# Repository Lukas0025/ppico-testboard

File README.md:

# PPICO V1 Test Board
Simple test board for ppico satellite project. Can be used as sattelite testboard and groud station. The board contains two ports for i2c devices and one port for programming and debugging. The board contains one lorawan transceiver, attiny85 as MCU, coin cell battery for power supply and PCB antenna for easy use, or connector for external antenna.

The board was designed to be usable as a LoRaWAN node.

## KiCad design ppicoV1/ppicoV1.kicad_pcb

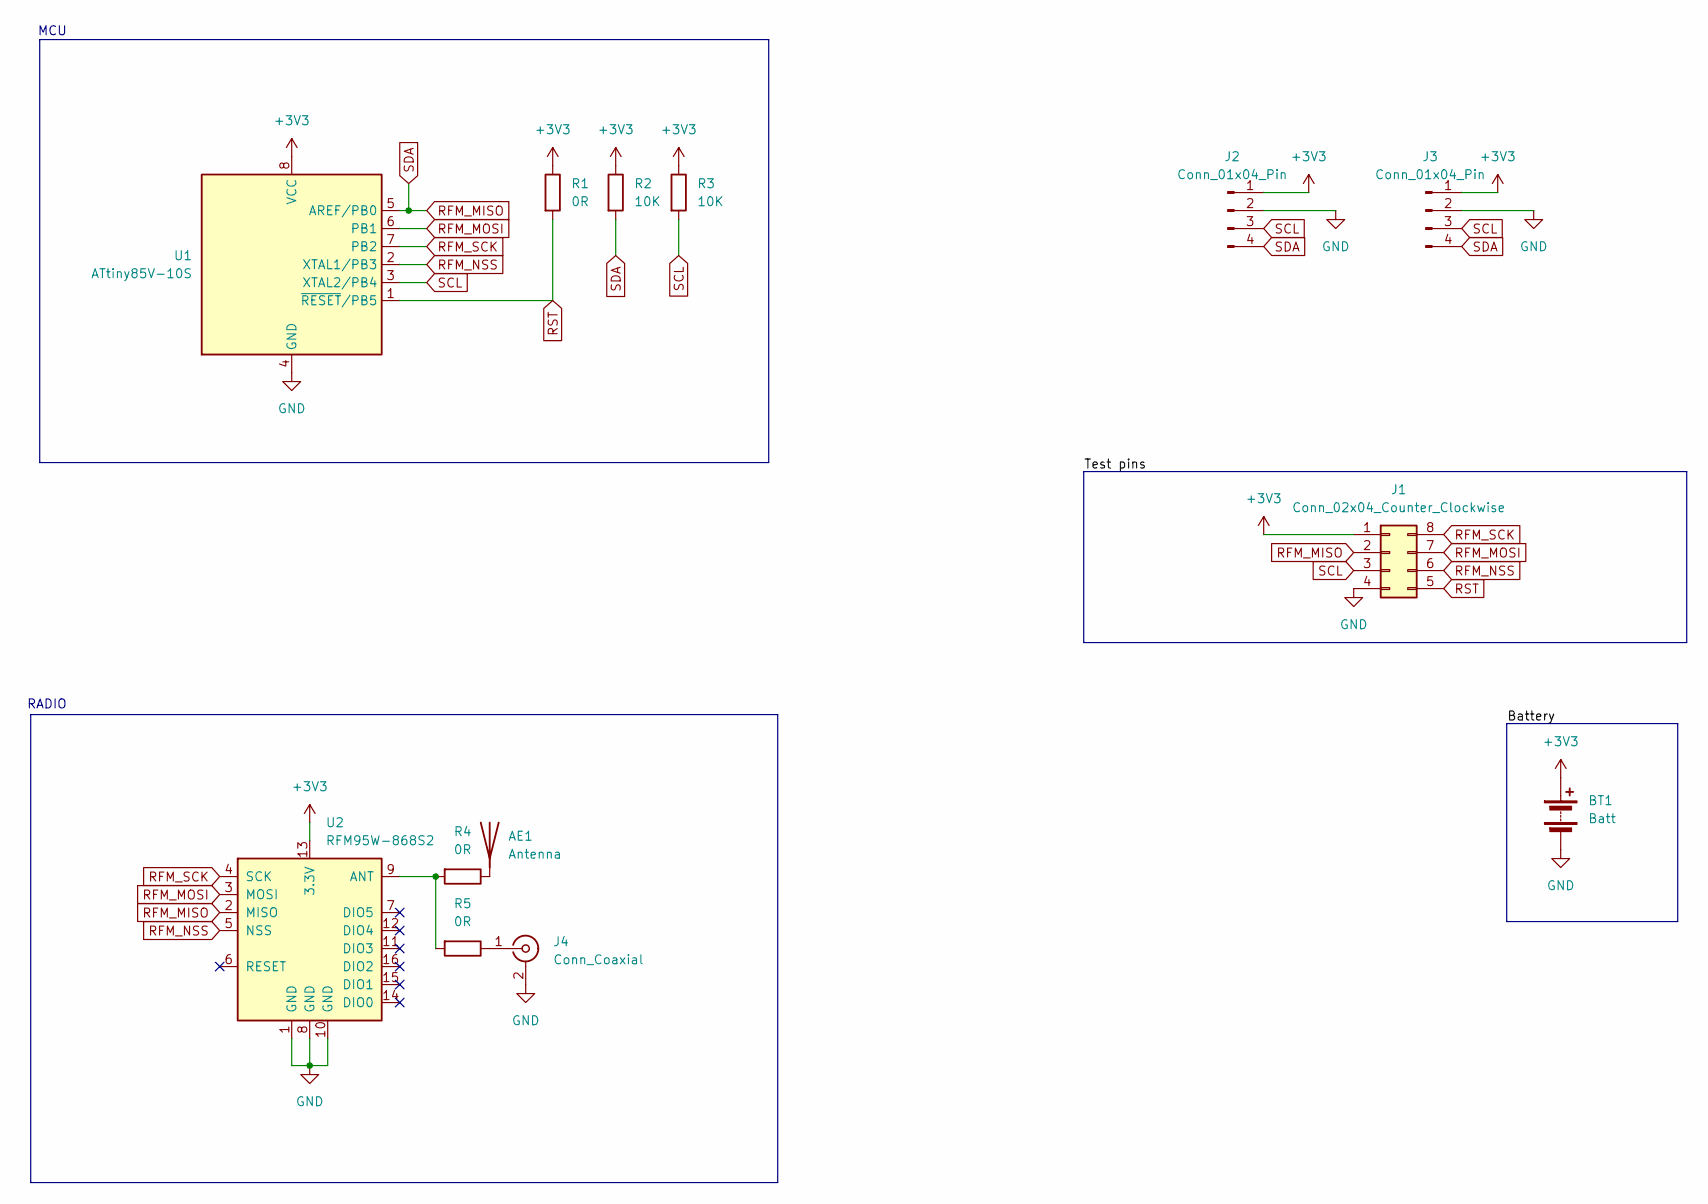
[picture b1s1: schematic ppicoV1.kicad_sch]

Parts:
AE1: Antenna; Texas_SWRA416_868MHz_915MHz
BT1: Batt; BatteryHolder_MYOUNG_BS-07-A1BJ001_CR2032
J1: Conn_02x04_Counter_Clockwise; PinHeader_2x04_P2.54mm_Vertical
J2, J3: Conn_01x04_Pin; PinHeader_1x04_P2.54mm_Vertical
J4: Conn_Coaxial; U.FL_Molex_MCRF_73412-0110_Vertical
R1, R4, R5: 0R; C_0805_2012Metric_Pad1.18x1.45mm_HandSolder
R2, R3: 10K; C_0805_2012Metric_Pad1.18x1.45mm_HandSolder
U1: ATtiny85V-10S; SOIC-8_5.3x5.3mm_P1.27mm
U2: RFM95W-868S2; HOPERF_RFM9XW_SMD

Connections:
+3V3: BT1.1 (+), J1.1, J2.1, J3.1, R1.1, R2.1, R3.1, U1.8 (VCC), U2.13 (3.3V)
GND: BT1.2 (-), J1.4, J2.2, J3.2, J4.2 (Ext), U1.4 (GND), U2.1 (GND), U2.8 (GND), U2.10 (GND)
unnamed: AE1.1 (A), R4.1
unnamed: J4.1 (In), R5.1
unnamed: R4.2, R5.2, U2.9 (ANT)
RFM_MISO: J1.2, J2.4, J3.4, R2.2, U1.5 (AREF/PB0), U2.2 (MISO)
RFM_MOSI: J1.7, U1.6 (PB1), U2.3 (MOSI)
RFM_NSS: J1.6, U1.2 (XTAL1/PB3), U2.5 (NSS)
RFM_SCK: J1.8, U1.7 (PB2), U2.4 (SCK)
RST: J1.5, R1.2, U1.1 (~RESET/PB5)
SCL: J1.3, J2.3, J3.3, R3.2, U1.3 (XTAL2/PB4)

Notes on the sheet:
MCU
RADIO

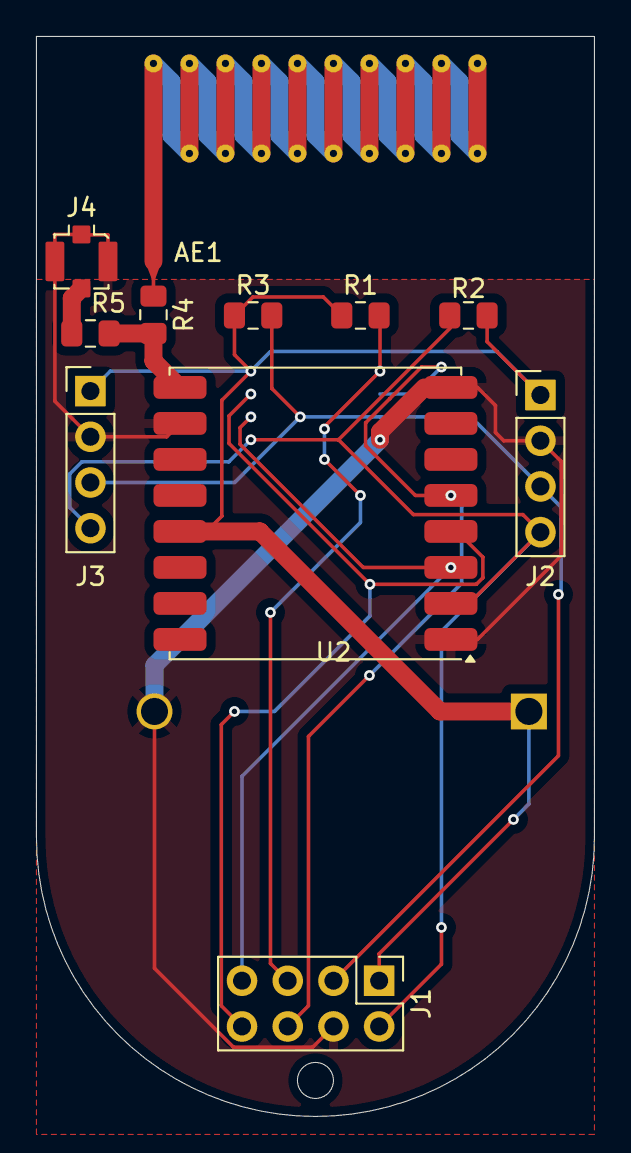
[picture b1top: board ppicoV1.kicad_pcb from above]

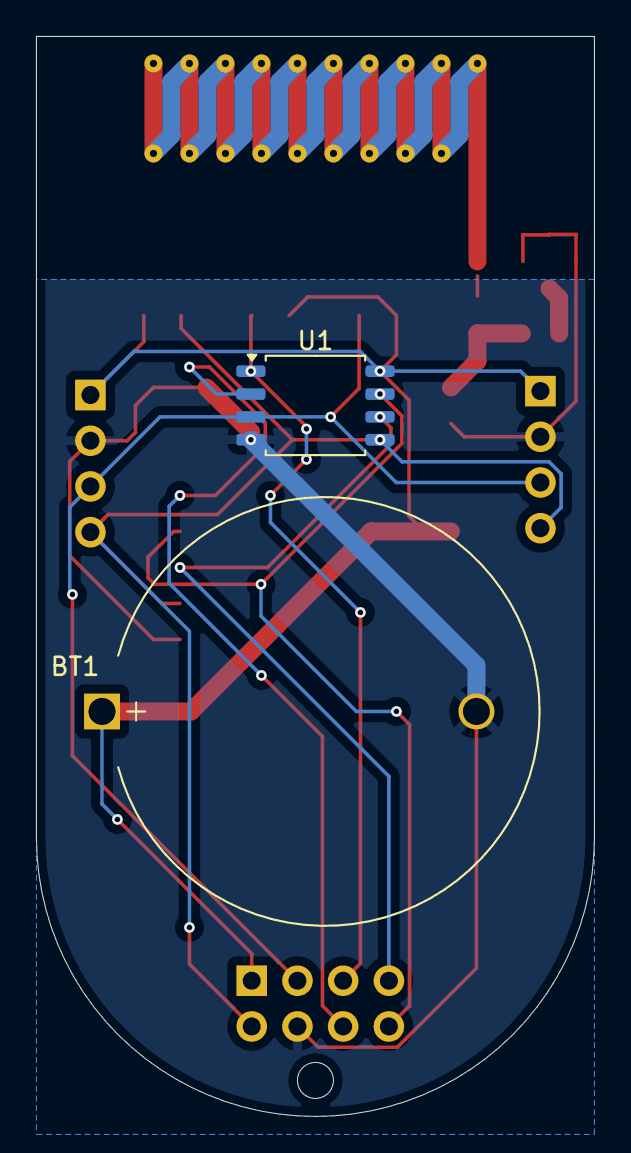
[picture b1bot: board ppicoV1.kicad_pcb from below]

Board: 2 copper layers, 31.0 x 60.0 mm, 13 parts (2 on the bottom side), 11 nets.
